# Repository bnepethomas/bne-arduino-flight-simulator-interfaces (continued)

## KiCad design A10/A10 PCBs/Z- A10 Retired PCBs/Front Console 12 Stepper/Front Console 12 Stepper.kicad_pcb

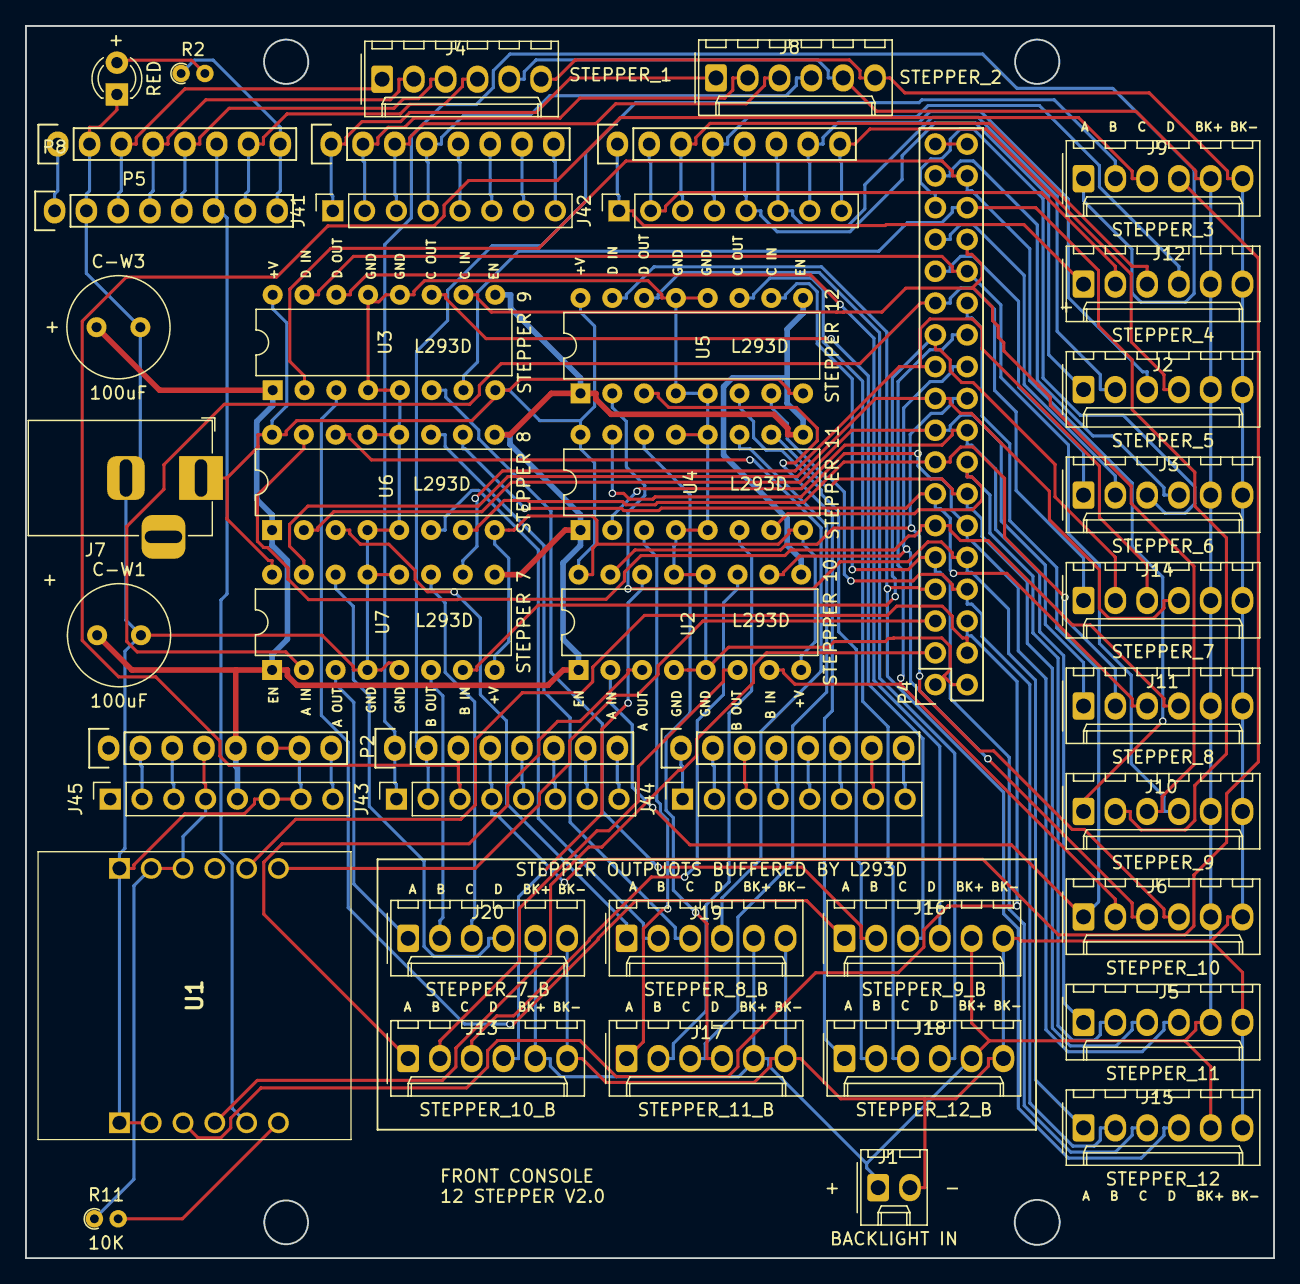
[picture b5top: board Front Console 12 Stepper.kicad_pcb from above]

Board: 2 copper layers, 99.7 x 98.4 mm, 45 parts (0 on the bottom side), 107 nets.

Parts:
C-W1, C-W3: 100uF; C_Radial_D8.0mm_H7.0mm_P3.50mm
D2: RED; LED_D3.0mm
J1: BACKLIGHT IN; Molex_KK-254_AE-6410-02A_1x02_P2.54mm_Vertical
J2: STEPPER_5; Molex_KK-254_AE-6410-06A_1x06_P2.54mm_Vertical
J3: STEPPER_6; Molex_KK-254_AE-6410-06A_1x06_P2.54mm_Vertical
J4: STEPPER_1; Molex_KK-254_AE-6410-06A_1x06_P2.54mm_Vertical
J5: STEPPER_11; Molex_KK-254_AE-6410-06A_1x06_P2.54mm_Vertical
J6: STEPPER_10; Molex_KK-254_AE-6410-06A_1x06_P2.54mm_Vertical
J7: STEPPER 5V; BarrelJack_Horizontal
J8: STEPPER_2; Molex_KK-254_AE-6410-06A_1x06_P2.54mm_Vertical
J9: STEPPER_3; Molex_KK-254_AE-6410-06A_1x06_P2.54mm_Vertical
J10: STEPPER_9; Molex_KK-254_AE-6410-06A_1x06_P2.54mm_Vertical
J11: STEPPER_8; Molex_KK-254_AE-6410-06A_1x06_P2.54mm_Vertical
J12: STEPPER_4; Molex_KK-254_AE-6410-06A_1x06_P2.54mm_Vertical
J13: STEPPER_10_B; Molex_KK-254_AE-6410-06A_1x06_P2.54mm_Vertical
J14: STEPPER_7; Molex_KK-254_AE-6410-06A_1x06_P2.54mm_Vertical
J15: STEPPER_12; Molex_KK-254_AE-6410-06A_1x06_P2.54mm_Vertical
J16: STEPPER_9_B; Molex_KK-254_AE-6410-06A_1x06_P2.54mm_Vertical
J17: STEPPER_11_B; Molex_KK-254_AE-6410-06A_1x06_P2.54mm_Vertical
J18: STEPPER_12_B; Molex_KK-254_AE-6410-06A_1x06_P2.54mm_Vertical
J19: STEPPER_8_B; Molex_KK-254_AE-6410-06A_1x06_P2.54mm_Vertical
J20: STEPPER_7_B; Molex_KK-254_AE-6410-06A_1x06_P2.54mm_Vertical
J41: PWM; PinSocket_1x08_P2.54mm_Vertical
J42: Communication; PinSocket_1x08_P2.54mm_Vertical
J43, J44: Analog; PinSocket_1x08_P2.54mm_Vertical
J45: Power; PinSocket_1x08_P2.54mm_Vertical
P1: Power; Socket_Strip_Arduino_1x08
P2, P3: Analog; Socket_Strip_Arduino_1x08
P4: Digital; Socket_Strip_Arduino_2x18
P5, P6, P8: PWM; Socket_Strip_Arduino_1x08
P7: Communication; Socket_Strip_Arduino_1x08
R2: 330; R_Axial_DIN0204_L3.6mm_D1.6mm_P1.90mm_Vertical
R11: 10K; R_Axial_DIN0204_L3.6mm_D1.6mm_P1.90mm_Vertical
U1: USR-ES1; USRES1
U2: STEPPPER 10; DIP-16_W7.62mm
U3: STEPPER 9; DIP-16_W7.62mm
U4: STEPPER 11; DIP-16_W7.62mm
U5: STEPPER 12; DIP-16_W7.62mm
U6: STEPPER 8; DIP-16_W7.62mm
U7: STEPPER 7; DIP-16_W7.62mm

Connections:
+3V3: J45.4, P1.4, R11.1, U1.B2 (3V3_1), U1.B3 (3V3_2)
+5VL: C-W1.1, C-W3.1, J45.5, P1.5, U2.1 (EN1,2), U2.9 (EN3,4), U3.1 (EN1,2), U3.9 (EN3,4), U4.1 (EN1,2), U4.9 (EN3,4), U5.1 (EN1,2), U5.9 (EN3,4), U6.1 (EN1,2), U6.9 (EN3,4), U7.1 (EN1,2), U7.9 (EN3,4)
/*2: J41.6, P6.6
/*3: J41.5, P6.5
/*4: J8.4, J41.4, P6.4
/*5: J8.3, J41.3, P6.3
/*6: J8.2, J41.2, P6.2
/*7: J8.1, J41.1, P6.1
/*8: P5.8, P8.8, R2.1
/*9: J4.4, P5.7, P8.7
/*11: J4.3, P5.5, P8.5
/*12: J4.2, P5.4, P8.4
/*13: J4.1, P5.3, P8.3
/A0: J9.1, J43.1, P2.1
/A1: J9.2, J43.2, P2.2
/A2: J9.3, J43.3, P2.3
/A3: J9.4, J43.4, P2.4
/A4: J43.5, P2.5
/A5: J43.6, P2.6
/A6: J43.7, P2.7
/A7: J43.8, P2.8
/A8: J44.1, P3.1
/A9: J44.2, P3.2
/A10: J44.3, P3.3
/A11: J44.4, P3.4
/A12: J44.5, P3.5
/A13: J44.6, P3.6
/A14: J44.7, P3.7
/A15: J44.8, P3.8
/AREF: P5.1, P8.1
/IOREF: J45.2, P1.2
/RX0/0: J41.8, P6.8
/RX1/19: J2.2, J42.6, P7.6
/RX2/17: J12.4, J42.4, P7.4
/RX3/15: J12.2, J42.2, P7.2
/Reset: J45.3, P1.3
/SCL/21: J2.4, J42.8, P7.8
/SDA/20: J2.3, J42.7, P7.7
/STEPPER_4_A: J12.1, J42.1, P7.1
/STEPPER_4_C: J12.3, J42.3, P7.3
/STEPPER_5_A: J2.1, J42.5, P7.5
/TX0/1: J41.7, P6.7
BACKLIGHT_LED+: J1.1, J2.5, J3.5, J4.5, J5.5, J6.5, J8.5, J9.5, J10.5, J11.5, J12.5, J13.5, J14.5, J15.5, J16.5, J17.5, J18.5, J19.5, J20.5
BACKLIGHT_LED-: J1.2, J2.6, J3.6, J4.6, J5.6, J6.6, J8.6, J9.6, J10.6, J11.6, J12.6, J13.6, J14.6, J15.6, J16.6, J17.6, J18.6, J19.6, J20.6
ES1_RST: P4.4, U1.B5 (RST)
GND: C-W1.2, C-W3.2, D2.1 (K), J7.2, J45.6, J45.7, P1.6, P1.7, P4.1, P4.2, P5.2, P8.2, U1.A1 (GND_1), U1.A2 (GND_2), U1.B1 (GND_3), U2.4 (GND), U2.5 (GND), U2.12 (GND), U2.13 (GND), U3.4 (GND), U3.5 (GND), U3.12 (GND), U3.13 (GND), U4.4 (GND), U4.5 (GND), U4.12 (GND), U4.13 (GND), U5.4 (GND), U5.5 (GND), U5.12 (GND), U5.13 (GND), U6.4 (GND), U6.5 (GND), U6.12 (GND), U6.13 (GND), U7.4 (GND), U7.5 (GND), U7.12 (GND), U7.13 (GND)
MISO: P4.5, U1.B6 (MISO)
MOSI: P4.6, U1.A3 (MOSI)
unnamed: D2.2 (A), R2.2
unnamed: J13.1, U2.3 (1Y)
unnamed: J13.2, U2.6 (2Y)
unnamed: J13.3, U2.11 (3Y)
unnamed: J13.4, U2.14 (4Y)
unnamed: J16.1, U3.3 (1Y)
unnamed: J16.2, U3.6 (2Y)
unnamed: J16.3, U3.11 (3Y)
unnamed: J16.4, U3.14 (4Y)
unnamed: J17.1, U4.3 (1Y)
unnamed: J17.2, U4.6 (2Y)
unnamed: J17.3, U4.11 (3Y)
unnamed: J17.4, U4.14 (4Y)
unnamed: J18.1, U5.3 (1Y)
unnamed: J18.2, U5.6 (2Y)
unnamed: J18.3, U5.11 (3Y)
unnamed: J18.4, U5.14 (4Y)
unnamed: J19.1, U6.3 (1Y)
unnamed: J19.2, U6.6 (2Y)
unnamed: J19.3, U6.11 (3Y)
unnamed: J19.4, U6.14 (4Y)
unnamed: J20.1, U7.3 (1Y)
unnamed: J20.2, U7.6 (2Y)
unnamed: J20.3, U7.11 (3Y)
unnamed: J20.4, U7.14 (4Y)
unnamed: P4.35, P4.36
unnamed: R11.2, U1.A6 (INT)
SCLK: P4.3, U1.A4 (SCLK)
SS: P5.6, P8.6, U1.A5 (CS)
STEP_V+: J7.1, U2.8 (VCC2), U2.16 (VCC1), U3.8 (VCC2), U3.16 (VCC1), U4.8 (VCC2), U4.16 (VCC1), U5.8 (VCC2), U5.16 (VCC1), U6.8 (VCC2), U6.16 (VCC1), U7.8 (VCC2), U7.16 (VCC1)
STPPER_6_A: J3.4, P4.33
STPPER_6_B: J3.3, P4.31
STPPER_6_C: J3.2, P4.29
STPPER_6_D: J3.1, P4.27
STPPER_7_A: J14.1, P4.25, U7.2 (1A)
STPPER_7_B: J14.2, P4.23, U7.7 (2A)
STPPER_7_C: J14.3, P4.21, U7.10 (3A)
STPPER_7_D: J14.4, P4.19, U7.15 (4A)
STPPER_8_A: J11.1, P4.17, U6.2 (1A)
STPPER_8_B: J11.2, P4.15, U6.7 (2A)
STPPER_8_C: J11.3, P4.13, U6.10 (3A)
STPPER_8_D: J11.4, P4.11, U6.15 (4A)
STPPER_9_A: J10.1, P4.34, U3.2 (1A)
STPPER_9_B: J10.2, P4.32, U3.7 (2A)
STPPER_9_C: J10.3, P4.30, U3.10 (3A)
STPPER_9_D: J10.4, P4.28, U3.15 (4A)
STPPER_10_A: J6.1, P4.26, U2.2 (1A)
STPPER_10_B: J6.2, P4.24, U2.7 (2A)
STPPER_10_C: J6.3, P4.22, U2.10 (3A)
STPPER_10_D: J6.4, P4.20, U2.15 (4A)
STPPER_11_A: J5.1, P4.18, U4.2 (1A)
STPPER_11_B: J5.2, P4.16, U4.7 (2A)
STPPER_11_C: J5.3, P4.14, U4.10 (3A)
STPPER_11_D: J5.4, P4.12, U4.15 (4A)
STPPER_12_A: J15.1, P4.10, U5.2 (1A)
STPPER_12_B: J15.2, P4.8, U5.7 (2A)
STPPER_12_C: J15.3, P4.9, U5.10 (3A)
STPPER_12_D: J15.4, P4.7, U5.15 (4A)
VCC: J45.8, P1.8

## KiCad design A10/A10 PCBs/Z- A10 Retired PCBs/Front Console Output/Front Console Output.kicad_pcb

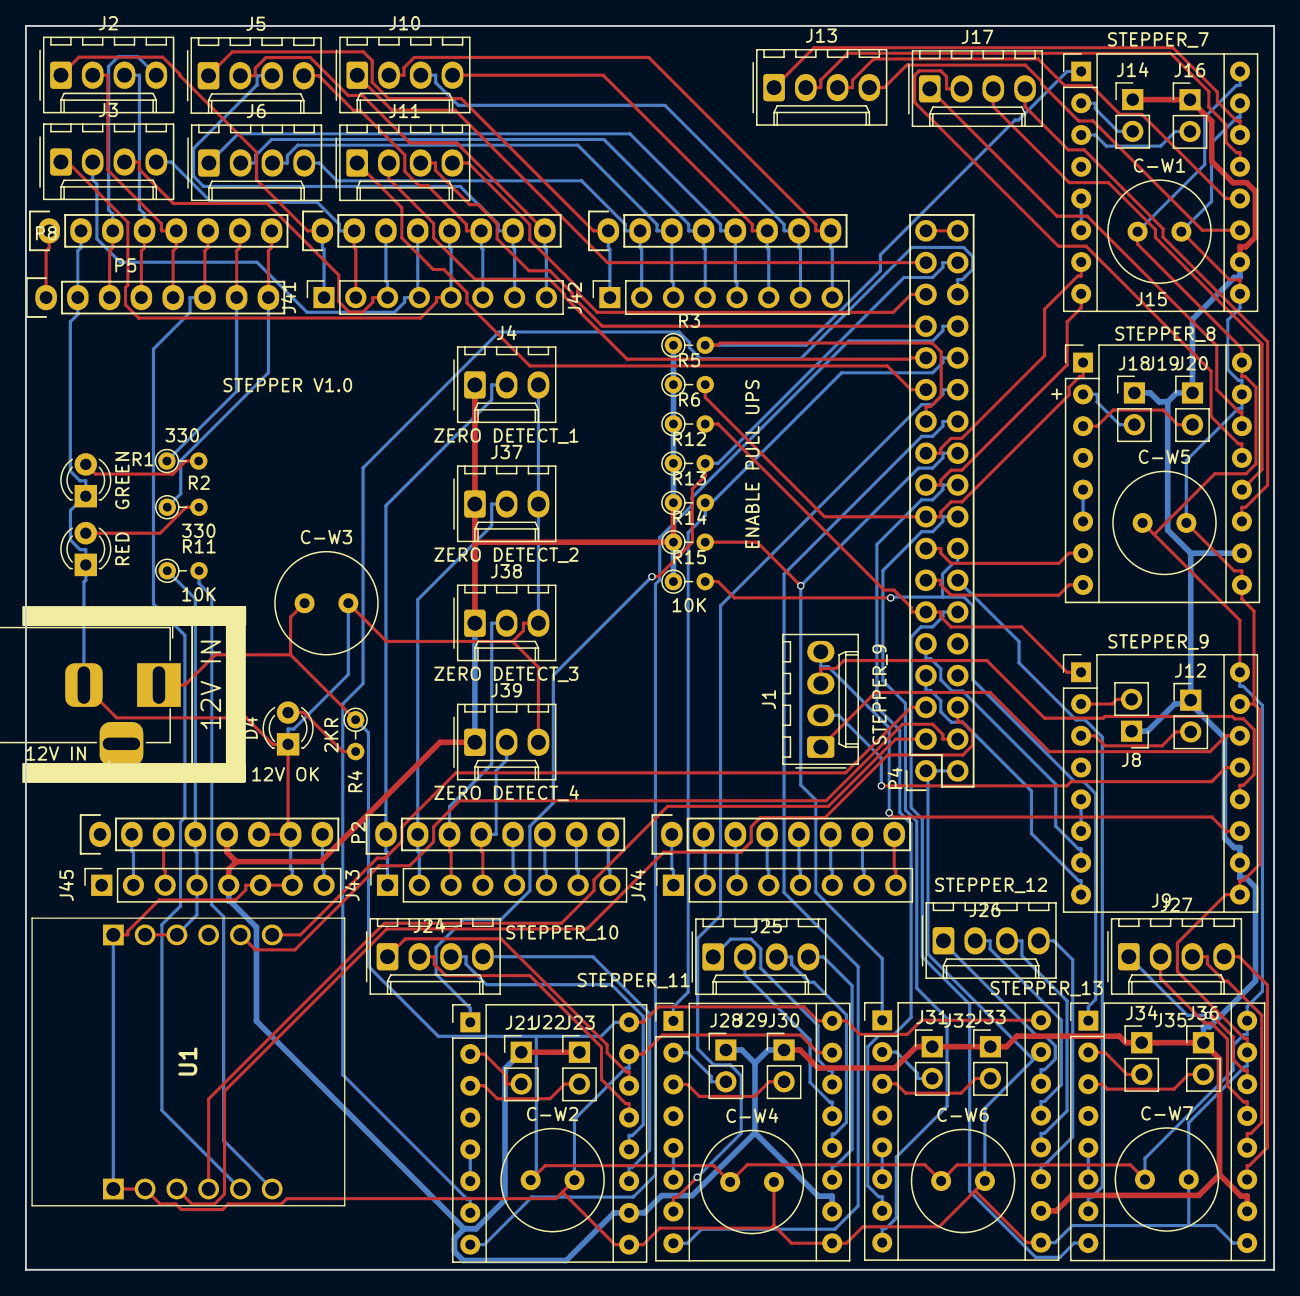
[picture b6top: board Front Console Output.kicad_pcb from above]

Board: 2 copper layers, 99.8 x 99.5 mm, 74 parts (0 on the bottom side), 130 nets.

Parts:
C-W1, C-W2, C-W3, C-W4, C-W5, C-W6, C-W7: 100uF; C_Radial_D8.0mm_H7.0mm_P3.50mm
D1: GREEN; LED_D3.0mm
D2: RED; LED_D3.0mm
D4: LED; LED_D3.0mm
J1: STEPPER_9; Molex_KK-254_AE-6410-04A_1x04_P2.54mm_Vertical
J2: STEPPER_1; Molex_KK-254_AE-6410-04A_1x04_P2.54mm_Vertical
J3: STEPPER_2; Molex_KK-254_AE-6410-04A_1x04_P2.54mm_Vertical
J4: ZERO DETECT_1; Molex_KK-254_AE-6410-03A_1x03_P2.54mm_Vertical
J5: STEPPER_3; Molex_KK-254_AE-6410-04A_1x04_P2.54mm_Vertical
J6: STEPPER_4; Molex_KK-254_AE-6410-04A_1x04_P2.54mm_Vertical
J7: STEPPER IN 12-20VDC; BarrelJack_Horizontal
J8: 9_MS1; PinHeader_1x02_P2.54mm_Vertical
J9: STEPPER_9; Pololu_Breakout-16_15.2x20.3mm
J10: STEPPER_5; Molex_KK-254_AE-6410-04A_1x04_P2.54mm_Vertical
J11: STEPPER_6; Molex_KK-254_AE-6410-04A_1x04_P2.54mm_Vertical
J12: 9_MS2; PinHeader_1x02_P2.54mm_Vertical
J13: STEPPER_7; Molex_KK-254_AE-6410-04A_1x04_P2.54mm_Vertical
J14: 7_MS1; PinHeader_1x02_P2.54mm_Vertical
J15: STEPPER_7; Pololu_Breakout-16_15.2x20.3mm
J16: 7_MS2; PinHeader_1x02_P2.54mm_Vertical
J17: STEPPER_8; Molex_KK-254_AE-6410-04A_1x04_P2.54mm_Vertical
J18: 8_MS1; PinHeader_1x02_P2.54mm_Vertical
J19: STEPPER_8; Pololu_Breakout-16_15.2x20.3mm
J20: 8_MS2; PinHeader_1x02_P2.54mm_Vertical
J21: 10_MS1; PinHeader_1x02_P2.54mm_Vertical
J22: STEPPER_10; Pololu_Breakout-16_15.2x20.3mm
J23: 10_MS2; PinHeader_1x02_P2.54mm_Vertical
J24: STEPPER_10; Molex_KK-254_AE-6410-04A_1x04_P2.54mm_Vertical
J25: STEPPER_11; Molex_KK-254_AE-6410-04A_1x04_P2.54mm_Vertical
J26: STEPPER_12; Molex_KK-254_AE-6410-04A_1x04_P2.54mm_Vertical
J27: STEPPER_13; Molex_KK-254_AE-6410-04A_1x04_P2.54mm_Vertical
J28: 11_MS1; PinHeader_1x02_P2.54mm_Vertical
J29: STEPPER_11; Pololu_Breakout-16_15.2x20.3mm
J30: 11_MS2; PinHeader_1x02_P2.54mm_Vertical
J31: 12_MS1; PinHeader_1x02_P2.54mm_Vertical
J32: STEPPER_12; Pololu_Breakout-16_15.2x20.3mm
J33: 12_MS2; PinHeader_1x02_P2.54mm_Vertical
J34: 13_MS1; PinHeader_1x02_P2.54mm_Vertical
J35: STEPPER_13; Pololu_Breakout-16_15.2x20.3mm
J36: 13_MS2; PinHeader_1x02_P2.54mm_Vertical
J37: ZERO DETECT_2; Molex_KK-254_AE-6410-03A_1x03_P2.54mm_Vertical
J38: ZERO DETECT_3; Molex_KK-254_AE-6410-03A_1x03_P2.54mm_Vertical
J39: ZERO DETECT_4; Molex_KK-254_AE-6410-03A_1x03_P2.54mm_Vertical
J41: PWM; PinSocket_1x08_P2.54mm_Vertical
J42: Communication; PinSocket_1x08_P2.54mm_Vertical
J43, J44: Analog; PinSocket_1x08_P2.54mm_Vertical
J45: Power; PinSocket_1x08_P2.54mm_Vertical
P1: Power; Socket_Strip_Arduino_1x08
P2, P3: Analog; Socket_Strip_Arduino_1x08
P4: Digital; Socket_Strip_Arduino_2x18
P5, P6, P8: PWM; Socket_Strip_Arduino_1x08
P7: Communication; Socket_Strip_Arduino_1x08
R1: 330; R_Axial_DIN0204_L3.6mm_D1.6mm_P2.54mm_Vertical
R2: 330; PT_R_Axial_DIN0204_L3.6mm_D1.6mm_P2.54mm_Vertical
R3, R5, R6, R12, R13, R14, R15: 10K; R_Axial_DIN0204_L3.6mm_D1.6mm_P2.54mm_Vertical
R4: 2000; R_Axial_DIN0204_L3.6mm_D1.6mm_P2.54mm_Vertical
R11: 10K; PT_R_Axial_DIN0204_L3.6mm_D1.6mm_P2.54mm_Vertical
U1: USR-ES1; USRES1

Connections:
+3V3: J45.4, P1.4, R11.1, U1.B2 (3V3_1), U1.B3 (3V3_2)
+5VL: J4.1, J8.1, J9.10, J12.1, J14.1, J15.10, J16.1, J18.1, J19.10, J20.1, J21.1, J22.10, J23.1, J28.1, J29.10, J30.1, J31.1, J32.10, J33.1, J34.1, J35.10, J36.1, J37.1, J38.1, J39.1, J45.5, P1.5, R3.1, R5.1, R6.1, R12.1, R13.1, R14.1, R15.1
/7_DIR: J15.8, P4.19
/7_EN: J15.1, P4.23, R3.2
/7_MS1: J14.2, J15.2
/7_MS2: J15.3, J16.2
/7_STEP: J15.7, P4.21
/8_DIR: J19.8, P4.13
/8_EN: J19.1, P4.17, R5.2
/8_MS1: J18.2, J19.2
/8_MS2: J19.3, J20.2
/8_STEP: J19.7, P4.15
/9_DIR: J9.8, P4.7
/9_EN: J9.1, P4.11, R6.2
/9_MS1: J8.2, J9.2
/9_MS2: J9.3, J12.2
/9_STEP: J9.7, P4.9
/10_DIR: J22.8, P4.30
/10_EN: J22.1, P4.34, R12.2
/10_MS1: J21.2, J22.2
/10_MS2: J22.3, J23.2
/10_STEP: J22.7, P4.32
/11_DIR: J29.8, P4.24
/11_EN: J29.1, P4.28, R13.2
/11_MS1: J28.2, J29.2
/11_MS2: J29.3, J30.2
/11_STEP: J29.7, P4.26
/12_DIR: J32.8, P4.18
/12_EN: J32.1, P4.22, R14.2
/12_MS1: J31.2, J32.2
/12_MS2: J32.3, J33.2
/12_STEP: J32.7, P4.20
/13_DIR: J35.8, P4.12
/13_EN: J35.1, P4.16, R15.2
/13_MS1: J34.2, J35.2
/13_MS2: J35.3, J36.2
/13_STEP: J35.7, P4.14
/*2: J5.4, J41.6, P6.6
/*3: J3.1, J41.5, P6.5
/*4: J3.2, J41.4, P6.4
/*5: J3.3, J41.3, P6.3
/*6: J3.4, J41.2, P6.2
/*7: J2.1, J41.1, P6.1
/*8: P5.8, P8.8, R2.1
/*9: P5.7, P8.7, R1.1
/*11: J2.2, P5.5, P8.5
/*12: J2.3, P5.4, P8.4
/*13: J2.4, P5.3, P8.3
/A0: J4.2, J43.1, P2.1
/A1: J37.2, J43.2, P2.2
/A2: J38.2, J43.3, P2.3
/A3: J39.2, J43.4, P2.4
/A4: J43.5, P2.5
/A5: J43.6, P2.6
/A6: J43.7, P2.7
/A7: J43.8, P2.8
/A8: J44.1, P3.1
/A9: J44.2, P3.2
/A10: J44.3, P3.3
/A11: J44.4, P3.4
/A12: J44.5, P3.5
/A13: J44.6, P3.6
/A14: J44.7, P3.7
/A15: J44.8, P3.8
/AREF: P5.1, P8.1
/IOREF: J45.2, P1.2
/ROLL_STEP_V+: C-W1.1, C-W2.1, C-W3.1, C-W4.1, C-W5.1, C-W6.1, C-W7.1, J7.1, J9.16, J15.16, J19.16, J22.16, J29.16, J32.16, J35.16, R4.1
/RX0/0: J5.2, J41.8, P6.8
/RX1/19: J10.4, J42.6, P7.6
/RX2/17: J6.2, J42.4, P7.4
/RX3/15: J6.4, J42.2, P7.2
/Reset: J45.3, P1.3
/SCL/21: J10.2, J42.8, P7.8
/SDA/20: J10.3, J42.7, P7.7
/STEPPER_3_B: J5.3, J41.7, P6.7
/STEPPER_3_D: J5.1, J42.1, P7.1
/STEPPER_4_B: J6.3, J42.3, P7.3
/STEPPER_4_D: J6.1, J42.5, P7.5
/STEPPER_5_D: J10.1, P4.33
/STEPPER_6_A: J11.4, P4.31
/STEPPER_6_B: J11.3, P4.29
/STEPPER_6_C: J11.2, P4.27
/STEPPER_6_D: J11.1, P4.25
/STEPPER_7_A: J13.4, J15.11
/STEPPER_7_B: J13.3, J15.12
/STEPPER_7_C: J13.2, J15.13
/STEPPER_7_D: J13.1, J15.14
/STEPPER_8_A: J17.4, J19.11
/STEPPER_8_B: J17.3, J19.12
/STEPPER_8_C: J17.2, J19.13
/STEPPER_8_D: J17.1, J19.14
/STEPPER_9_A: J1.4, J9.11
/STEPPER_9_B: J1.3, J9.12
/STEPPER_9_C: J1.2, J9.13
/STEPPER_9_D: J1.1, J9.14
/STEPPER_10_A: J22.11, J24.4
/STEPPER_10_B: J22.12, J24.3
/STEPPER_10_C: J22.13, J24.2
/STEPPER_10_D: J22.14, J24.1
/STEPPER_11_A: J25.4, J29.11
/STEPPER_11_B: J25.3, J29.12
/STEPPER_11_C: J25.2, J29.13
/STEPPER_11_D: J25.1, J29.14
/STEPPER_12_A: J26.4, J32.11
/STEPPER_12_B: J26.3, J32.12
/STEPPER_12_C: J26.2, J32.13
/STEPPER_12_D: J26.1, J32.14
/STEPPER_13_A: J27.4, J35.11
/STEPPER_13_B: J27.3, J35.12
/STEPPER_13_C: J27.2, J35.13
/STEPPER_13_D: J27.1, J35.14
ES1_RST: P4.4, U1.B5 (RST)
GND: C-W1.2, C-W2.2, C-W3.2, C-W4.2, C-W5.2, C-W6.2, C-W7.2, D1.1 (K), D2.1 (K), D4.1 (K), J4.3, J7.2, J9.9, J9.15, J15.9, J15.15, J19.9, J19.15, J22.9, J22.15, J29.9, J29.15, J32.9, J32.15, J35.9, J35.15, J37.3, J38.3, J39.3, J45.6, J45.7, P1.6, P1.7, P4.1, P4.2, P5.2, P8.2, U1.A1 (GND_1), U1.A2 (GND_2), U1.B1 (GND_3)
MISO: P4.5, U1.B6 (MISO)
MOSI: P4.6, U1.A3 (MOSI)
unnamed: D1.2 (A), R1.2
unnamed: D2.2 (A), R2.2
unnamed: D4.2 (A), R4.2
unnamed: J9.5, J9.6
unnamed: J15.5, J15.6
unnamed: J19.5, J19.6
unnamed: J22.5, J22.6
unnamed: J29.5, J29.6
unnamed: J32.5, J32.6
unnamed: J35.5, J35.6
unnamed: P4.35, P4.36
unnamed: R11.2, U1.A6 (INT)
SCLK: P4.3, U1.A4 (SCLK)
SS: P5.6, P8.6, U1.A5 (CS)
VCC: J45.8, P1.8

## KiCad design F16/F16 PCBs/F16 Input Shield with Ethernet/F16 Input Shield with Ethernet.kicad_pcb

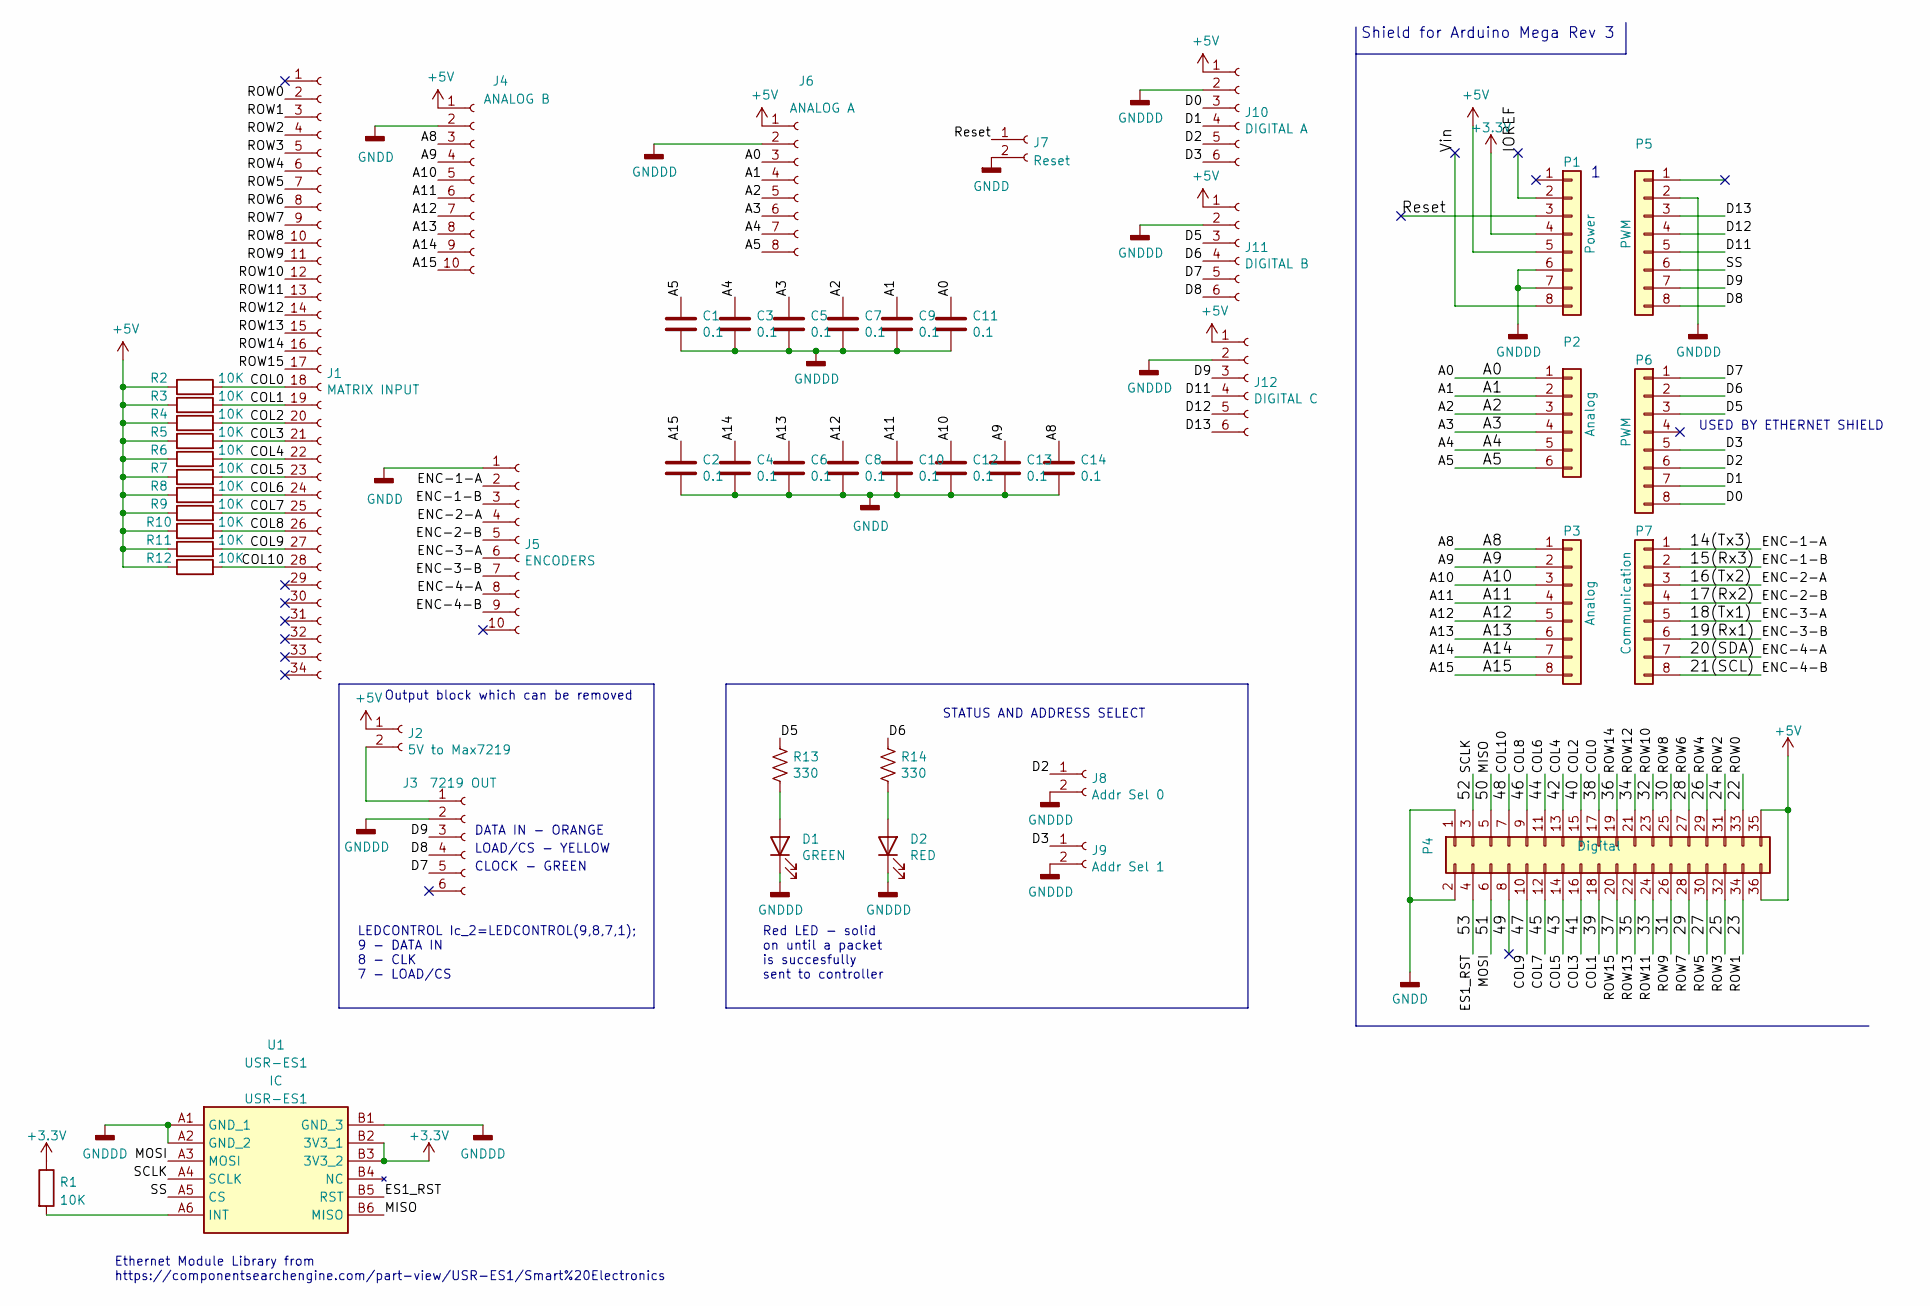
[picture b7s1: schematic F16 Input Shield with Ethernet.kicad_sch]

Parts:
C1, C2, C3, C4, C5, C6, C7, C8, C9, C10, C11, C12, C13, C14: 0.1; C_Disc_D6.0mm_W2.5mm_P5.00mm
D1: GREEN; LED_D3.0mm
D2: RED; LED_D3.0mm
J1: MATRIX INPUT; IDC-Header_2x17_P2.54mm_Vertical
J2: 5V to Max7219; Molex_1x02_P2.54mm_Vertical
J3: 7219 OUT; Molex_1x06_P2.54mm_Vertical
J4: ANALOG B; Molex_1x10_P2.54mm_Vertical
J5: ENCODERS; Molex_1x10_P2.54mm_Vertical
J6: ANALOG A; Molex_1x08_P2.54mm_Vertical
J7: Reset; PinHeader_1x02_P2.54mm_Vertical
J8: Addr Sel 0; PinHeader_1x02_P2.54mm_Vertical
J9: Addr Sel 1; PinHeader_1x02_P2.54mm_Vertical
J10: DIGITAL A; Molex_1x06_P2.54mm_Vertical
J11: DIGITAL B; Molex_1x06_P2.54mm_Vertical
J12: DIGITAL C; Molex_1x06_P2.54mm_Vertical
P1: Power; Socket_Strip_Arduino_1x08
P2: Analog; PinHeader_1x06_P2.54mm_Vertical
P3: Analog; Socket_Strip_Arduino_1x08
P4: Digital; Socket_Strip_Arduino_2x18
P5, P6: PWM; Socket_Strip_Arduino_1x08
P7: Communication; Socket_Strip_Arduino_1x08
R1, R2, R3, R4, R5, R6, R7, R8, R9, R10, R11, R12: 10K; PT_R_Axial_DIN0204_L3.6mm_D1.6mm_P2.54mm_Vertical
R13, R14: 330; PT_R_Axial_DIN0204_L3.6mm_D1.6mm_P2.54mm_Vertical
U1: USR-ES1; USRES1; Manufacturer_Part_Number USR-ES1

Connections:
+3.3V: P1.4, R1.1, U1.B2 (3V3_1), U1.B3 (3V3_2)
+5V: J2.1, J4.1, J6.1, J10.1, J11.1, J12.1, P1.5, P4.35, P4.36, R2.1, R3.1, R4.1, R5.1, R6.1, R7.1, R8.1, R9.1, R10.1, R11.1, R12.1
/14(Tx3): J5.2, P7.1
/15(Rx3): J5.3, P7.2
/16(Tx2): J5.4, P7.3
/17(Rx2): J5.5, P7.4
/18(Tx1): J5.6, P7.5
/19(Rx1): J5.7, P7.6
/20(SDA): J5.8, P7.7
/21(SCL): J5.9, P7.8
/22: J1.2, P4.33
/23: J1.3, P4.34
/24: J1.4, P4.31
/25: J1.5, P4.32
/26: J1.6, P4.29
/27: J1.7, P4.30
/28: J1.8, P4.27
/29: J1.9, P4.28
/30: J1.10, P4.25
/31: J1.11, P4.26
/32: J1.12, P4.23
/33: J1.13, P4.24
/34: J1.14, P4.21
/35: J1.15, P4.22
/36: J1.16, P4.19
/37: J1.17, P4.20
/38: J1.18, P4.17, R2.2
/39: J1.19, P4.18, R3.2
/40: J1.20, P4.15, R4.2
/41: J1.21, P4.16, R5.2
/42: J1.22, P4.13, R6.2
/43: J1.23, P4.14, R7.2
/44: J1.24, P4.11, R8.2
/45: J1.25, P4.12, R9.2
/46: J1.26, P4.9, R10.2
/47: J1.27, P4.10, R11.2
/48: J1.28, P4.7, R12.2
/49: P4.8
/50: P4.5, U1.B6 (MISO)
/51: P4.6, U1.A3 (MOSI)
/52: P4.3, U1.A4 (SCLK)
/53: P4.4, U1.B5 (RST)
/A0: C11.1, J6.3, P2.1
/A1: C9.1, J6.4, P2.2
/A2: C7.1, J6.5, P2.3
/A3: C5.1, J6.6, P2.4
/A4: C3.1, J6.7, P2.5
/A5: C1.1, J6.8, P2.6
/A8: C14.1, J4.3, P3.1
/A9: C13.1, J4.4, P3.2
/A10: C12.1, J4.5, P3.3
/A11: C10.1, J4.6, P3.4
/A12: C8.1, J4.7, P3.5
/A13: C6.1, J4.8, P3.6
/A14: C4.1, J4.9, P3.7
/A15: C2.1, J4.10, P3.8
/D0: J10.3, P6.8
/D1: J10.4, P6.7
/D2: J8.1, J10.5, P6.6
/D3: J9.1, J10.6, P6.5
/D5: J11.3, P6.3, R13.1
/D6: J11.4, P6.2, R14.1
/D7: J3.5, J11.5, P6.1
/D8: J3.4, J11.6, P5.8
/D9: J3.3, J12.3, P5.7
/D11: J12.4, P5.5
/D12: J12.5, P5.4
/D13: J12.6, P5.3
/IOREF: P1.2
/Reset: J7.1, P1.3
/SS: P5.6, U1.A5 (CS)
/Vin: P1.8
unnamed: D1.2 (A), R13.2
unnamed: D2.2 (A), R14.2
unnamed: J2.2, J3.1
unnamed: R1.2, U1.A6 (INT)

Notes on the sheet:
LEDCONTROL Ic_2=LEDCONTROL(9,8,7,1); 9 - DATA IN 8 - CLK 7 - LOAD/CS
Ethernet Module Library from https://componentsearchengine.com/part-view/USR-ES1/Smart%20Electronics
Shield for Arduino Mega Rev 3
Red LED - solid on until a packet is succesfully sent to controller
LOAD/CS - YELLOW
DATA IN - ORANGE
Output block which can be removed
CLOCK - GREEN
USED BY ETHERNET SHIELD
STATUS AND ADDRESS SELECT

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
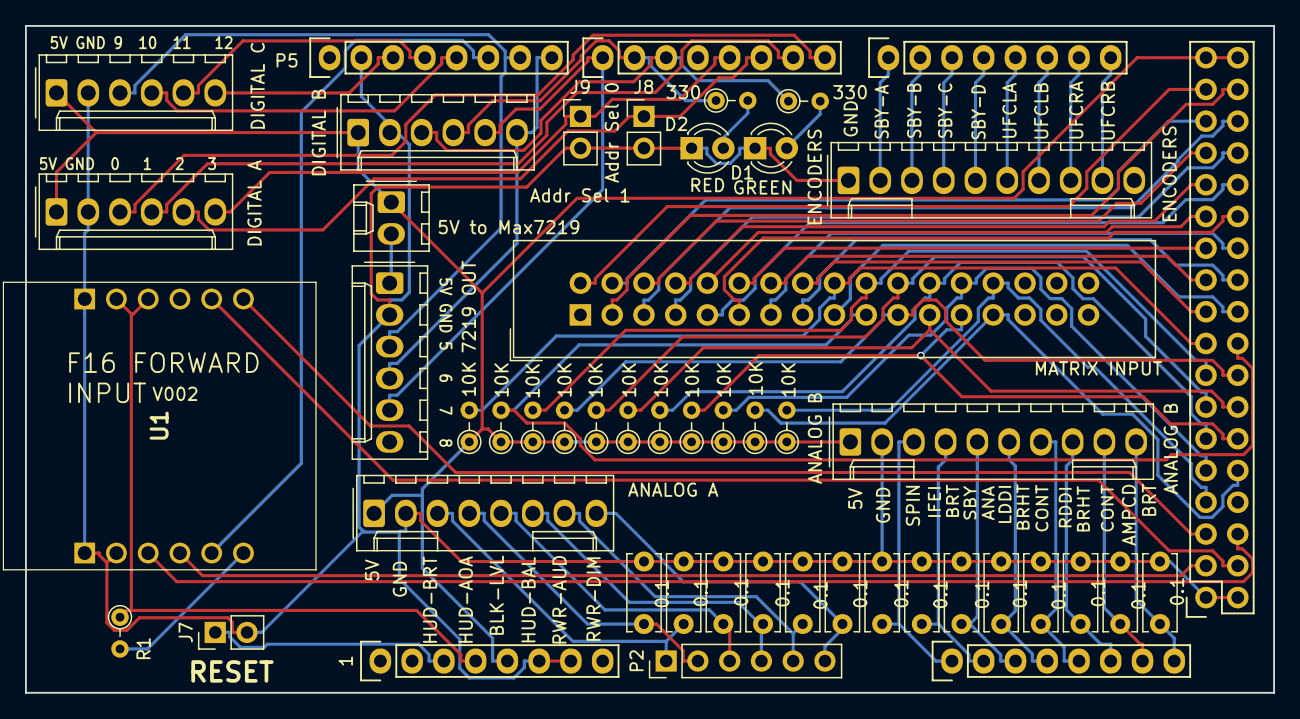
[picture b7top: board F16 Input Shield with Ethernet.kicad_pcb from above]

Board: 2 copper layers, 99.8 x 53.3 mm, 50 parts (0 on the bottom side), 74 nets.

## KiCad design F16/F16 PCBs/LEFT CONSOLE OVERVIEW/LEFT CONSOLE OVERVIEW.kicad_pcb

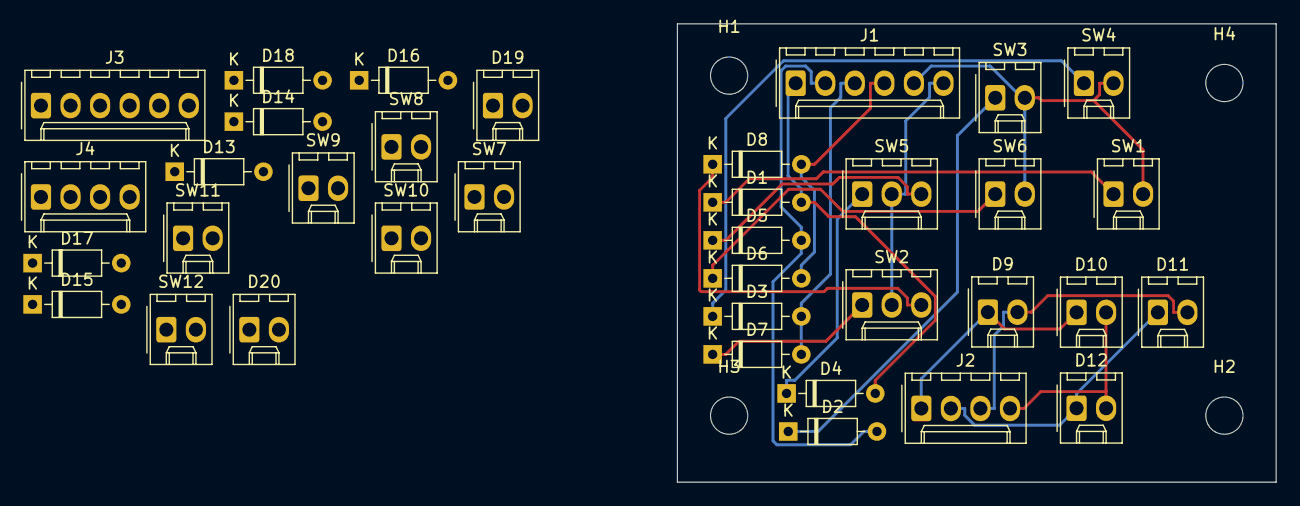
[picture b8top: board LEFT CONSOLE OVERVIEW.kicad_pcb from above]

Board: 2 copper layers, 51.4 x 39.4 mm, 40 parts (0 on the bottom side), 32 nets.

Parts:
D1, D2, D3, D4, D5, D6, D7, D8, D13, D14, D15, D16, D17, D18: D; D_Signal_P7.62mm_Horizontal
D9: L-C; Molex_1x02_P2.54mm_Vertical
D10, D11: R-A; Molex_1x02_P2.54mm_Vertical
D12: R-B; Molex_1x02_P2.54mm_Vertical
D19: RUN; Molex_1x02_P2.54mm_Vertical
D20: FAIL; Molex_1x02_P2.54mm_Vertical
H1, H2, H3, H4: MountingHole; MountingHole_3.2mm_M3
J1: TEST INPUTS; Molex_1x06_P2.54mm_Vertical
J2, J4: TEST LEDS; Molex_1x04_P2.54mm_Vertical
J3: FLT-CTL-INPUT; Molex_1x06_P2.54mm_Vertical
SW1: FIRE & OH DETECT; Molex_1x02_P2.54mm_Vertical
SW2: FLCS-TEST; Molex_1x03_P2.54mm_Vertical
SW3: OXY QTY; Molex_1x02_P2.54mm_Vertical
SW4: MAL & IND LTS; Molex_1x02_P2.54mm_Vertical
SW5: PROBE HEAT; Molex_1x03_P2.54mm_Vertical
SW6: EPU GEN; Molex_1x02_P2.54mm_Vertical
SW7: DIGITAL-BACKUP; Molex_1x02_P2.54mm_Vertical
SW8: ALT-FLAPS; Molex_1x02_P2.54mm_Vertical
SW9: MANUAL-TF; Molex_1x02_P2.54mm_Vertical
SW10: LE-FLAPS; Molex_1x02_P2.54mm_Vertical
SW11: FLCS-RESET; Molex_1x02_P2.54mm_Vertical
SW12: BIT; Molex_1x02_P2.54mm_Vertical

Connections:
/FLIGHT-CONTROL/FLT-CTL-COL-0: J3.3, SW7.2 (B), SW10.2 (B)
/FLIGHT-CONTROL/FLT-CTL-COL-1: J3.4, SW8.2 (B), SW11.2 (B)
/FLIGHT-CONTROL/FLT-CTL-COL-2: J3.5, SW9.2 (B), SW12.2 (B)
/FLIGHT-CONTROL/FLT-CTL-ROW-0: D13.2 (A), D14.2 (A), D15.2 (A)
/FLIGHT-CONTROL/FLT-CTL-ROW-1: D16.2 (A), D17.2 (A), D18.2 (A), J3.2
/FLIGHT-CONTROL/TEST-LED-COL-0: D19.2 (A), J4.2
/FLIGHT-CONTROL/TEST-LED-COL-1: D20.2 (A), J4.3
/FLIGHT-CONTROL/TEST-LED-ROW-0: D19.1 (K), D20.1 (K), J4.1
/Test/TEST-COL-0: J1.5, SW1.2, SW3.2 (B), SW4.2, SW6.2 (B)
/Test/TEST-COL-1: J1.6, SW2.2 (B), SW5.2 (B)
/Test/TEST-LED-COL-0: D9.2 (A), D11.2 (A), J2.3
/Test/TEST-LED-COL-1: D10.2 (A), D12.2 (A), J2.4
/Test/TEST-LED-ROW-0: D9.1 (K), D10.1 (K), J2.1
/Test/TEST-LED-ROW-1: D11.1 (K), D12.1 (K), J2.2
/Test/TEST-ROW-0: D1.2 (A), D4.2 (A), J1.1
/Test/TEST-ROW-1: D2.2 (A), D5.2 (A), J1.2
/Test/TEST-ROW-2: D3.2 (A), D7.2 (A), J1.3
/Test/TEST-ROW-3: D6.2 (A), D8.2 (A), J1.4
unnamed: D1.1 (K), SW1.1
unnamed: D2.1 (K), SW3.1 (A)
unnamed: D3.1 (K), SW4.1
unnamed: D4.1 (K), SW5.1 (A)
unnamed: D5.1 (K), SW5.3 (C)
unnamed: D6.1 (K), SW6.1 (A)
unnamed: D7.1 (K), SW2.1 (A)
unnamed: D8.1 (K), SW2.3 (C)
unnamed: D13.1 (K), SW7.1 (A)
unnamed: D14.1 (K), SW8.1 (A)
unnamed: D15.1 (K), SW9.1 (A)
unnamed: D16.1 (K), SW10.1 (A)
unnamed: D17.1 (K), SW11.1 (A)
unnamed: D18.1 (K), SW12.1 (A)
